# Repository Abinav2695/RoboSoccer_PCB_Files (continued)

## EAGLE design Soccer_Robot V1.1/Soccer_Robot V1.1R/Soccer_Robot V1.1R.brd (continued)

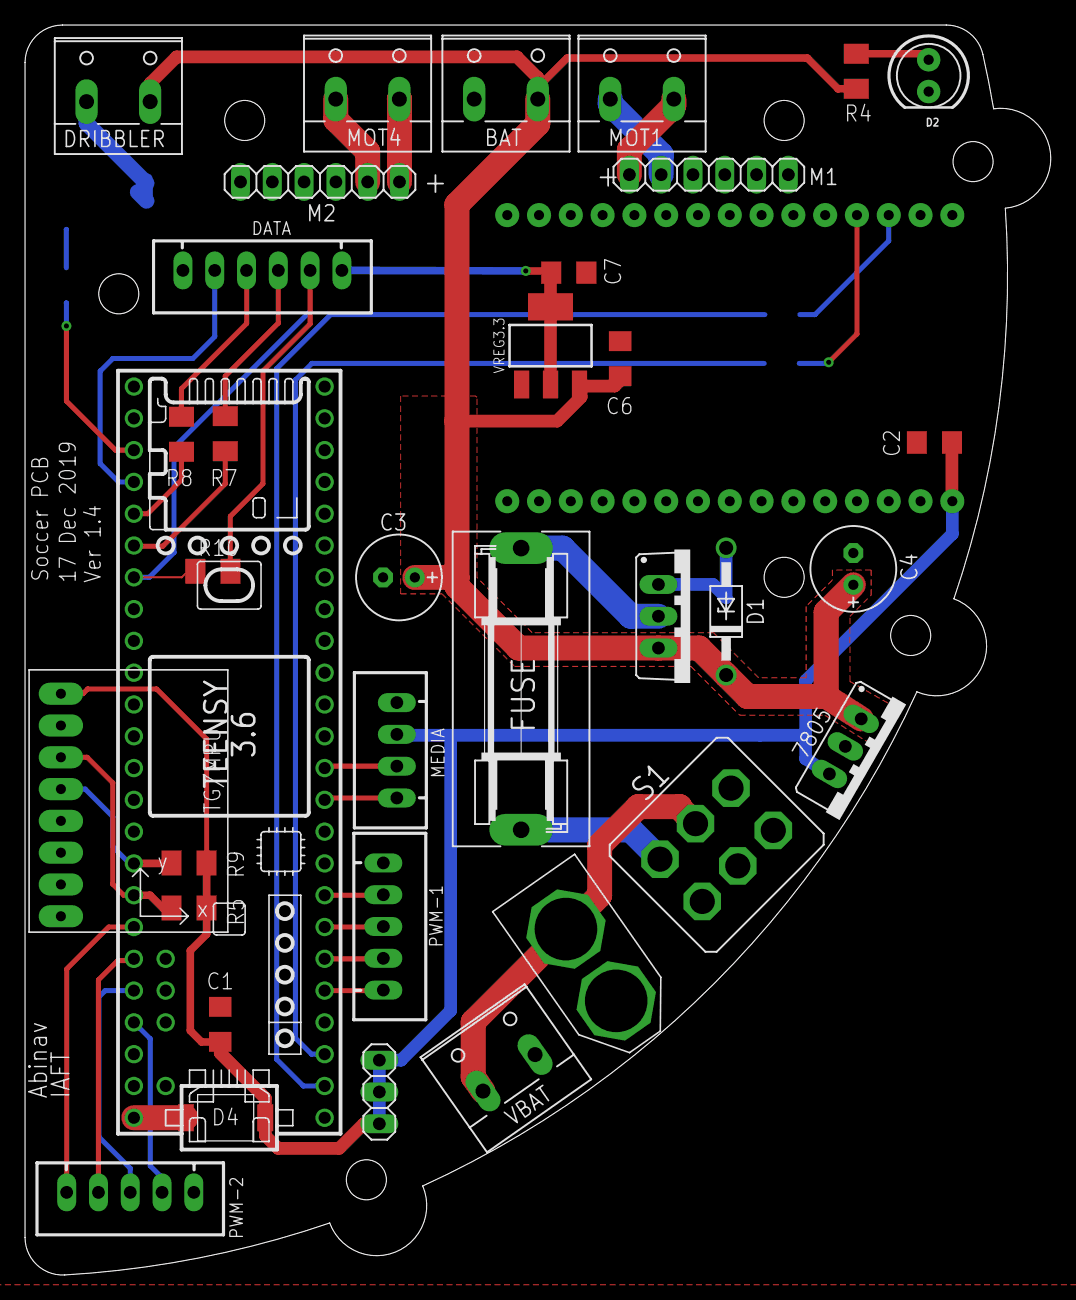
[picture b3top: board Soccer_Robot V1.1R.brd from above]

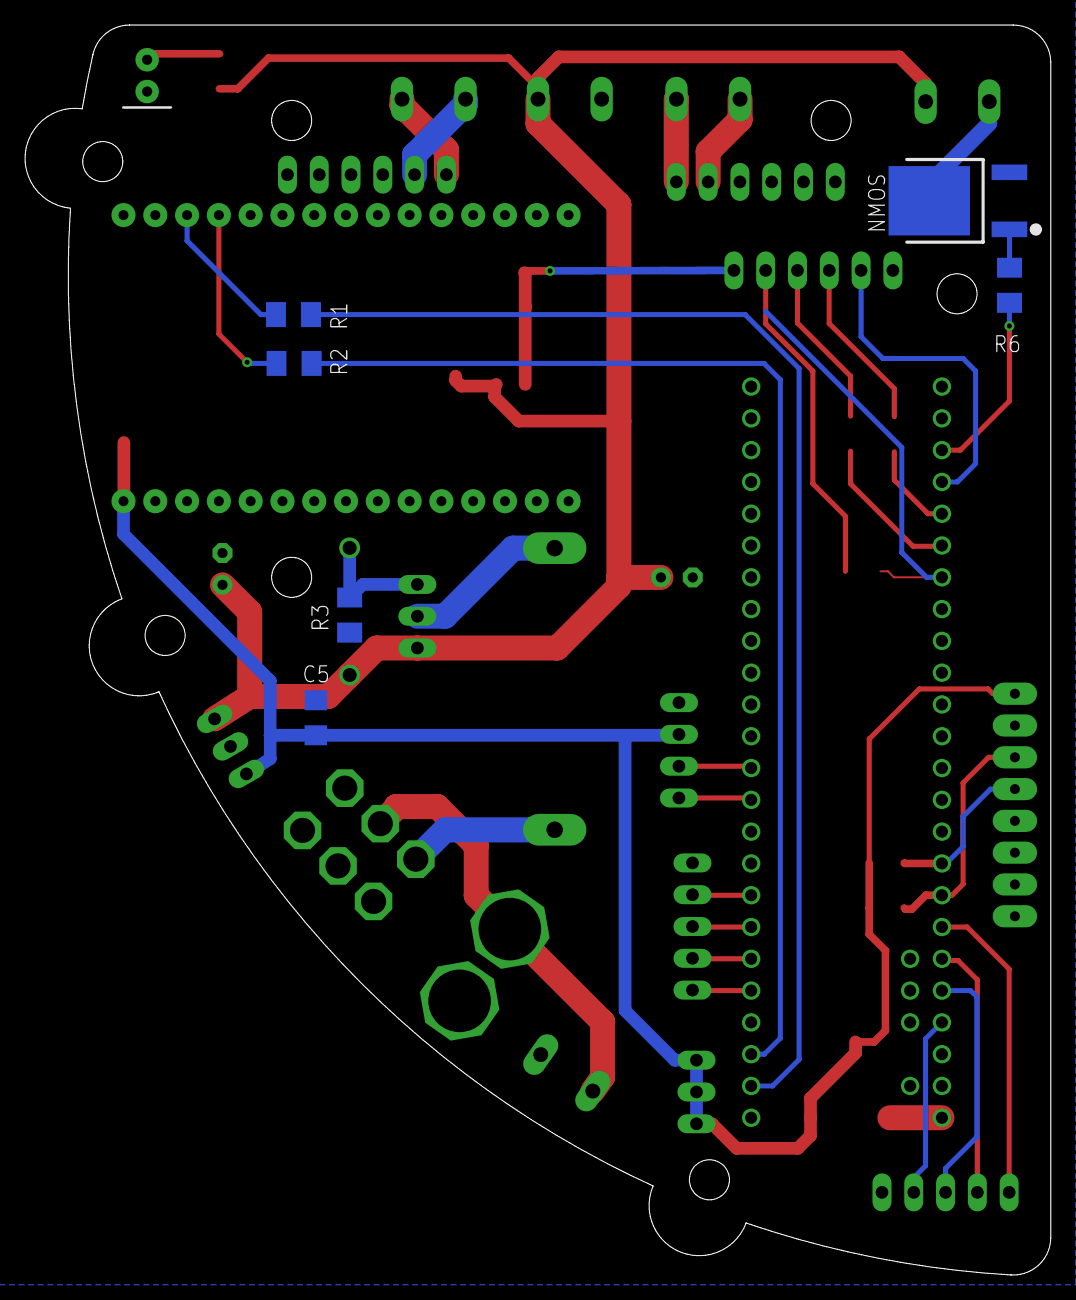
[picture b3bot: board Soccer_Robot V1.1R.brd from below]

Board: 2 copper layers, 82.0 x 99.9 mm, 42 parts (6 on the bottom side), 40 nets.

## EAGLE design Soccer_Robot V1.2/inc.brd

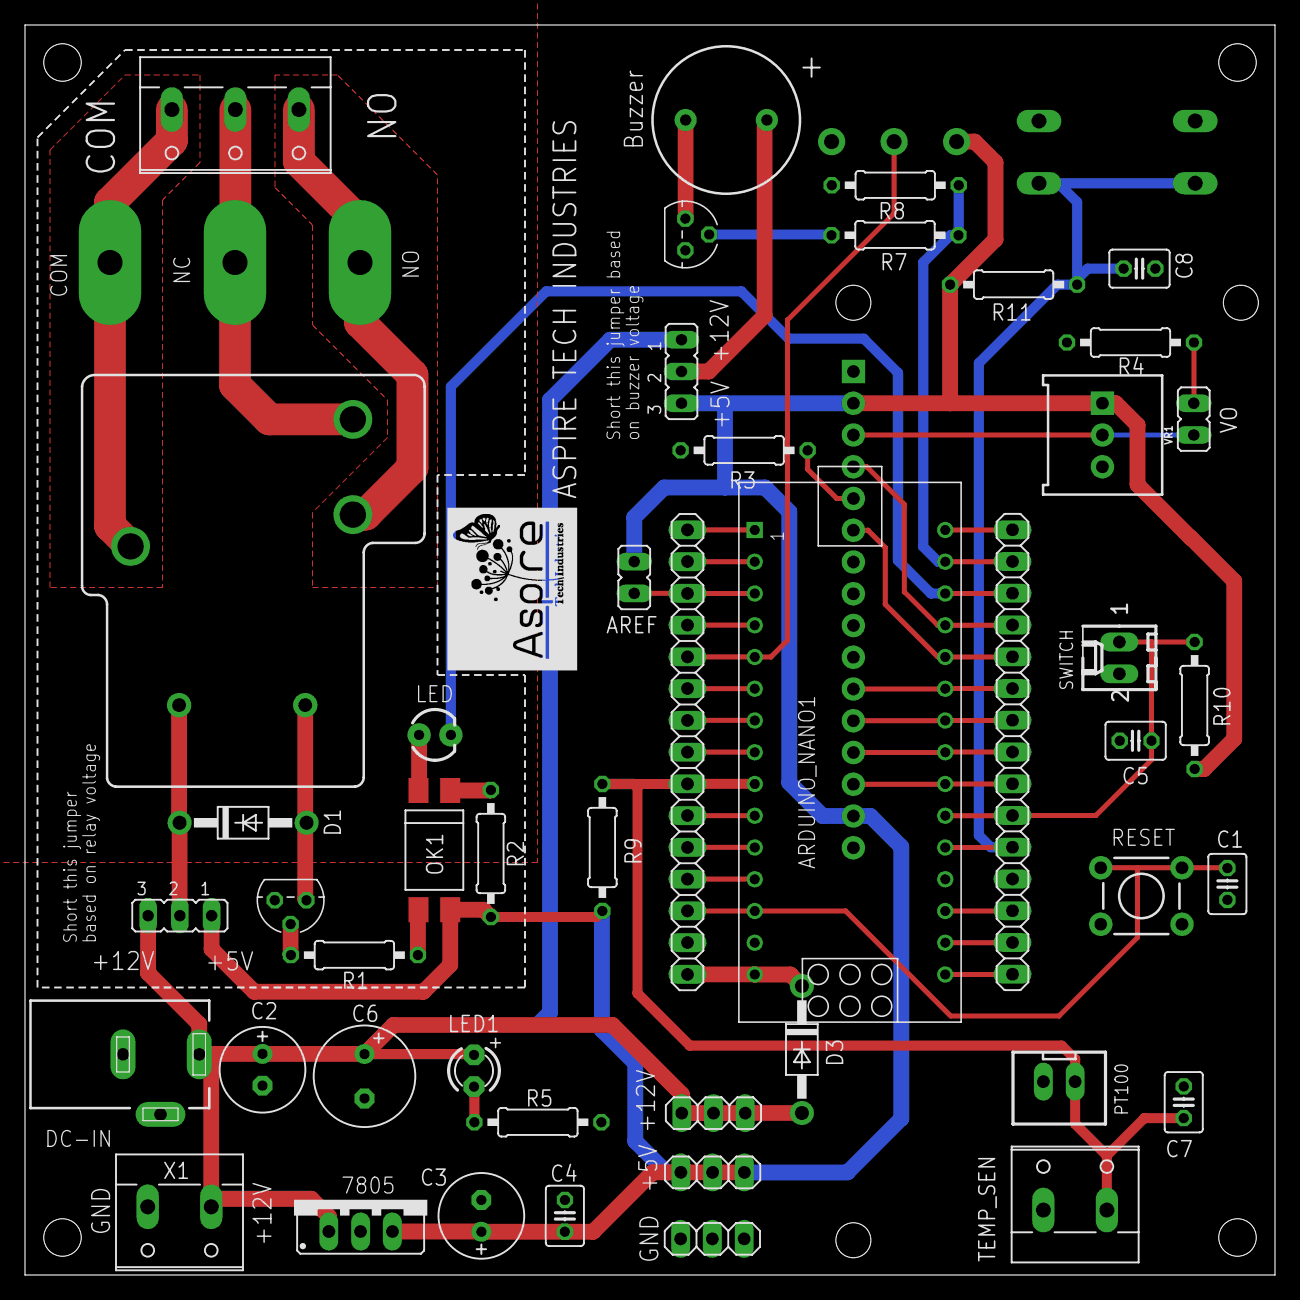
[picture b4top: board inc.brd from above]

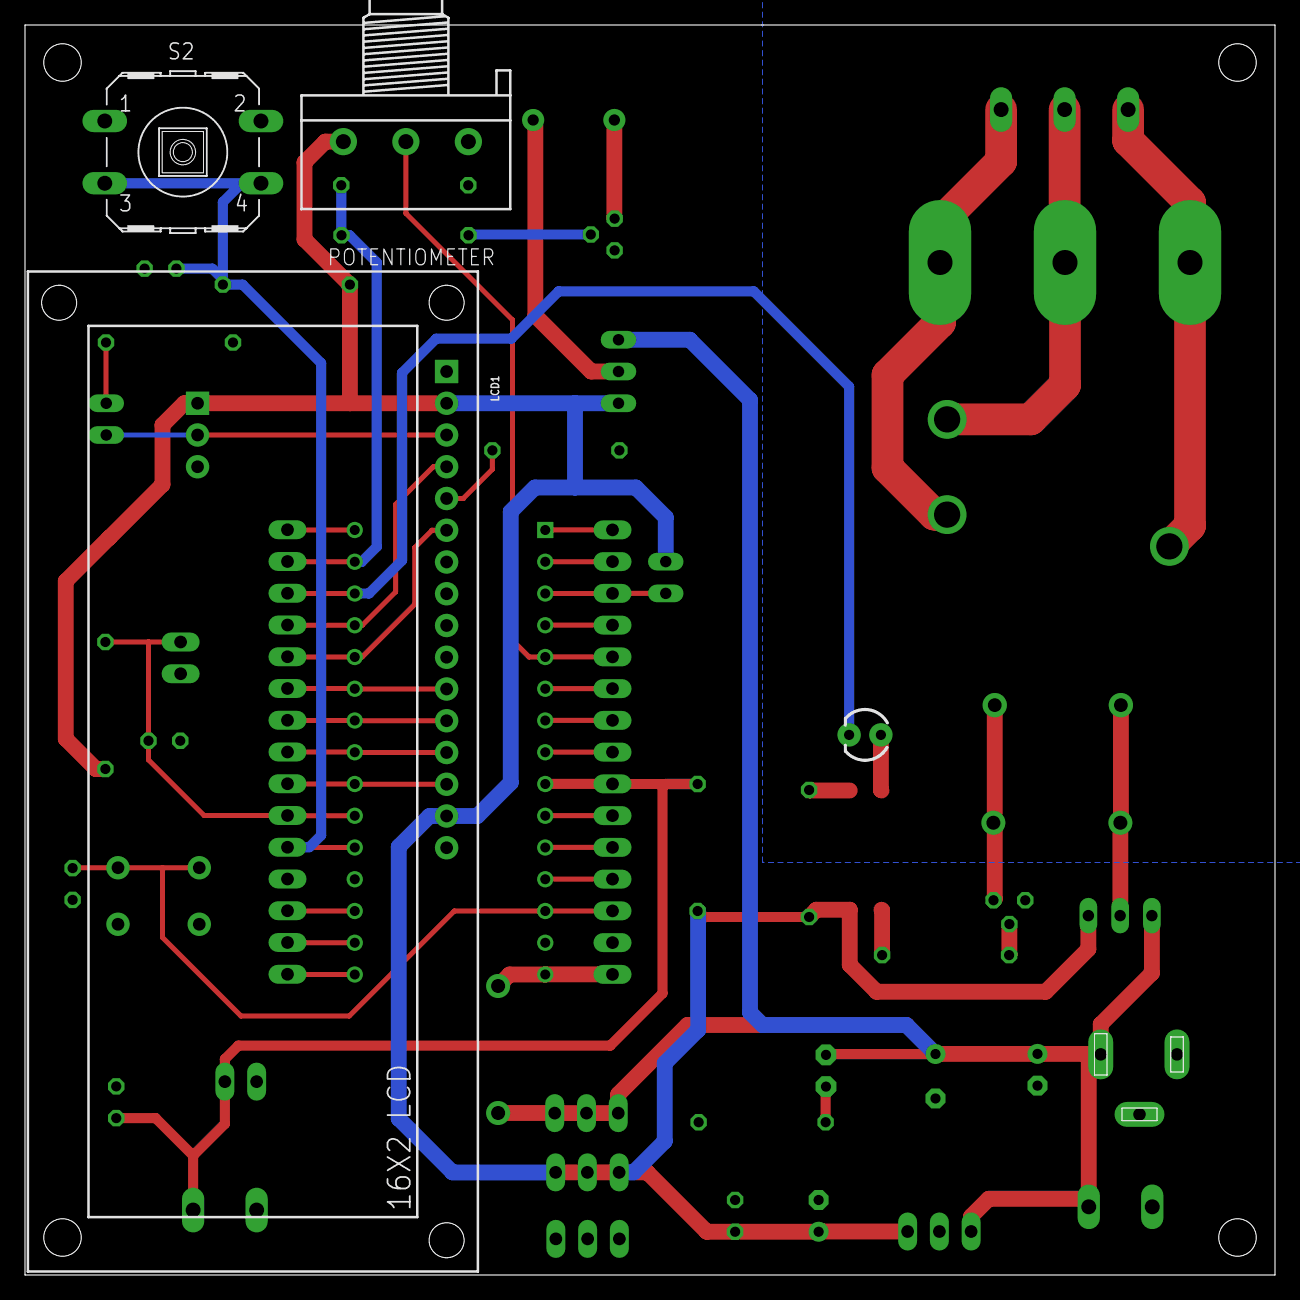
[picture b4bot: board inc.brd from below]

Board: 2 copper layers, 100.0 x 100.0 mm, 52 parts (3 on the bottom side), 47 nets.

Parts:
ARDUINO_NANO1: ARDUINO_NANO
AREF: JP1
C1, C5, C7, C8: 0.01uF; C025-030X050
C2: 47uF; E2,5-7
C3: 22uF; E2,5-7
C4: 0.1uF; C025-030X050
C6: 220uF; E3,5-8
COM: LPAD1
D1, D3: 1N4004; DO41-10
D2: LED_3MM
IC1: 78XXS
J4: DCJ0303
JP1, JP8: JP2
JP3, JP4: 1X15
JP5, JP6, JP7: 1X03
K1: RELAY-SPDT-JQX-15F; RELAY-T90
LCD1: LCD-16X2SILK; LCD-16X2
LED1: LED3MM
NC: LPAD1
NO: LPAD1
OK1: SFH6206; DIL4-SMD
PT100: JST-XH-02-PIN-LONG-PAD; JST-XH-02-PACKAGE-LONG-PAD
Q1: BC547; TO92
R1, R2, R3, R4, R7, R11: 100E; 0207/10
R5, R8: 1k; 0207/10
R9: 430E; 0207/10
R10: 1K; 0207/10
R12: 3RP/1610N
RELAY: W237-3E
S1: TACTILE-PTH
S2: B3F-40XX
SG2: BUZZERPTH; BUZZER-12MM
SWITCH: 22-27-2021-02; 6410-02
T1: BC547; TO92
TEMP_SEN: W237-132
VO: JP1
VR1: 10k; TRIMPOT-PTH-3386U
X1: W237-132

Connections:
+5V: AREF.2, C3.+, C4.1, IC1.OUT, JP1.1, JP6.1, JP6.2, JP6.3, JP8.3, LCD1.2, LCD1.15, OK1.4, R2.2, R9.2, R10.2, R11.2, R12.3, VR1.1
+12V: C2.+, C6.+, D3.A, IC1.IN, J4.1, JP1.3, JP5.1, JP5.2, JP5.3, JP8.1, LED1.A, X1.1
BUTTON: ARDUINO_NANO1.20, C8.1, JP3.5, R11.1, S2.3, S2.4
BUZZ: ARDUINO_NANO1.29, JP3.14, R7.1, R8.1
DATA1: ARDUINO_NANO1.25, JP3.10, LCD1.11
DATA2: ARDUINO_NANO1.24, JP3.9, LCD1.12
DATA3: ARDUINO_NANO1.23, JP3.8, LCD1.13
DATA4: ARDUINO_NANO1.22, JP3.7, LCD1.14
EN: ARDUINO_NANO1.26, JP3.11, LCD1.6
GND: ARDUINO_NANO1.14, ARDUINO_NANO1.19, C1.2, C2.-, C3.-, C4.2, C5.2, C6.-, C7.2, C8.2, IC1.GND, J4.2, J4.3, JP3.4, JP4.2, JP7.1, JP7.2, JP7.3, LCD1.1, LCD1.16, PT100.2, Q1.1, R3.2, R4.1, R5.1, R8.2, R12.1, S1.3, S1.4, S2.1, S2.2, SWITCH.2, T1.1, TEMP_SEN.1, VR1.3, X1.2
unnamed: D1.C, JP1.2, K1.COIL1
unnamed: D1.A, K1.COIL2, T1.3
unnamed: R1.2, T1.2
unnamed: OK1.3, R1.1
unnamed: OK1.1, R2.1
unnamed: D2.A, OK1.2
unnamed: ARDUINO_NANO1.4, JP4.12
unnamed: LCD1.5, R3.1
unnamed: LCD1.3, VO.2, VR1.2
unnamed: ARDUINO_NANO1.16, JP3.1
unnamed: R4.2, VO.1
unnamed: ARDUINO_NANO1.17, JP3.2
unnamed: ARDUINO_NANO1.18, JP3.3
unnamed: ARDUINO_NANO1.30, JP3.15
unnamed: ARDUINO_NANO1.12, JP4.4
unnamed: ARDUINO_NANO1.11, JP4.5
unnamed: ARDUINO_NANO1.10, JP4.6
unnamed: ARDUINO_NANO1.8, JP4.8
unnamed: ARDUINO_NANO1.7, JP4.9
unnamed: ARDUINO_NANO1.6, JP4.10
unnamed: ARDUINO_NANO1.3, AREF.1, JP4.13
unnamed: ARDUINO_NANO1.2, JP4.14
unnamed: ARDUINO_NANO1.1, JP4.15
unnamed: LED1.K, R5.2
unnamed: JP8.2, SG2.+
unnamed: Q1.3, SG2.-
unnamed: Q1.2, R7.2
POTIN: ARDUINO_NANO1.5, JP4.11, R12.2
RCOM: COM.1, K1.MAIN, RELAY.3
RELAY_SIG: ARDUINO_NANO1.28, D2.K, JP3.13
RESET: ARDUINO_NANO1.13, C1.1, JP4.3, S1.1, S1.2
RNC: K1.NC, NC.1, RELAY.2
RNO: K1.NO, NO.1, RELAY.1
RS: ARDUINO_NANO1.27, JP3.12, LCD1.4
SWITCH: ARDUINO_NANO1.21, C5.1, JP3.6, R10.1, SWITCH.1
TEMP_SIG: ARDUINO_NANO1.9, C7.1, JP4.7, PT100.1, R9.1, TEMP_SEN.2
VIN: ARDUINO_NANO1.15, D3.C, JP4.1

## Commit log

2023-05-21 pcb files
